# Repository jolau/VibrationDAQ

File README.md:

# VibrationDAQ
Data Acquisition (DAQ) of the [Analog Devices ADcmXL3021](https://www.analog.com/en/products/adcmxl3021.html#product-overview) vibration sensor. The VibrationDAQ was developed as part of an internship at [Wingtra](https://wingtra.com/) by [Jonas Lauener](https://www.jolau.ch/).  

**For any technical questions, please open an issue: https://github.com/jolau/VibrationDAQ/issues/new/choose**

Copyright (c) 2020, Jonas Lauener & Wingtra AG\

## Hardware
- Raspberry Pi 
- [Analog Devices ADcmXL3021](https://www.analog.com/en/products/adcmxl3021.html#product-overview) vibration sensor capabilities
    - [Corrected data sheet](docs/ADcmXL3021_corrected.pdf)
    - Sensor orientation:\
    
    - Mass: 13 g
    - Frequencies up to 110 kHz
    - ±50 g measurement range
    - MFFT mode: Spectral analysis through internal FFT\
    
        - 2048 bins per axis with user configurable bin sizes from 0.42 Hz to 53.7 Hz
        - Windowing options: rectangular, Hanning, flat top
    - MTC mode: Time domain capture\
    
        - 4096 samples per axis
- [Features a status LED](#status-led)

### Pinout Raspberry Pi

|       | pin | pin |       |
|-------|-----|-----|-------|
| RST 1 | 13  |     |       |
| BSY 1 | 15  | 16  | RST 2 |
| 3V3   | 17  | 18  | BSY 2 |
| MOSI  | 19  | 20  | EMPTY |
| MISO  | 21  | 22  | SYNC  |
| SCLK  | 23  | 24  | CE 1  |
| GND   | 25  | 26  | CE 2  |

The vibration sensor only works on the main SPI pins (SPI0) of the Raspberry Pi - the other SPI ports don't support SPI mode 3.

### Custom adapter board
The pins of the ADcmXL3021 vibration sensor can be accessed by using a custom adapter board. The PCB was created by using the software KiCad: [KiCad project files](ADcmXL3021_adapter/ADcmXL3021_adapter.pro)\

## Installation
_In case you want to setup your own VibrationDAQ on a Raspberry Pi:_
1. Install yaml-cpp (as described below)
2. Clone this repo.
3. `cd VibrationDAQ`
4. `mkdir build & cd build`
5. `cmake ..`
6. `sudo make install`

Make sure that you have [enabled SPI](https://www.raspberrypi-spy.co.uk/2014/08/enabling-the-spi-interface-on-the-raspberry-pi/).

You can use it now with `vibration_daq_app [full path to config.yaml]`.

#### Installation of yaml-cpp
1. `wget https://github.com/jbeder/yaml-cpp/archive/yaml-cpp-0.6.3.tar.gz`
2. `tar -xvf yaml-cpp-0.6.3.tar.gz`
3. `cd yaml-cpp-yaml-cpp-0.6.3/`
4. `mkdir build`
5. `cd build`
6. `cmake .. -DYAML_BUILD_SHARED_LIBS=ON`
7. `sudo make install`

### Enable/Disable auto-start
1. Edit config.yaml path in vibration_daq.service file to own needs 
2. `sudo systemctl enable [full path to vibration_daq.service file]`    
    This automatically links the service and enables it. Replace `enable` with `disable` to disable service.

## Dependencies
Many thanks to the authors of the following libraries:
- [yaml-cpp](https://github.com/jbeder/yaml-cpp)
- [loguru](https://github.com/emilk/loguru)
- [c-periphery](https://github.com/vsergeev/c-periphery)
- [date](https://github.com/HowardHinnant/date)

## Usage
### Workflow
1. Connect to the Raspberry Pi and adapt the `~/Documents/config.yaml` to your requirements. Make sure that auto-start is enabled. If it's the first time you use it, test it by running it manually: `vibration_daq_app [full path to config.yaml]`
2. Mount the vibration sensor with the double sided tape [3M™ Adhesive Transfer Tape 950](https://www.digikey.ch/product-detail/en/3m-tc/3-4-5-950/3M9743-ND/2649288). This shouldn't distort the vibration too much.
3. Do your measurement.
4. Download the collected data over SFTP. I recommend to also download the used config file.
6. Open a vibration CSV file in Google Sheets. 
    - For FFT measurement: 
        - Hide the first two data points as these have usually very high magnitude and don't give meaningful information
        - Plot the data using a column chart.  

### Status led
If the status led is enabled in config, it will glow when running:
- Constant glow: data acquisition is running normally
- Blink: measurement completed, saving data to a new csv file

## Config file
Short primer on the syntax of yaml: https://learnxinyminutes.com/docs/yaml/

### Decimation Filter
Setting the right `decimation_factor` is crucial for getting meaningful data. Choose it according to the maximum vibration frequency you're expecting.
Of course, the decimation factor also affects the predefined FIR filters i.e. with a FACTOR_64, the LOW_PASS_10kHz is actually a 156 Hz low pass filter.  
 
| **decimation_factor** | **Effective Sample Rate, fS (SPS)** | **Effective FFT Bin Size, f_MIN (Hz)** | **Effective Maximum FFT Frequency, f_MAX (Hz)** |
|-------------------|---------------------------------|------------------------------------|---------------------------------------------|
| FACTOR_1          | 220000                          | 53.71094                           | 110000                                      |
| FACTOR_2          | 110000                          | 26.85547                           | 55000                                       |
| FACTOR_4          | 55000                           | 13.42773                           | 27500                                       |
| FACTOR_8          | 27500                           | 6.713867                           | 13750                                       |
| FACTOR_16         | 13750                           | 3.356934                           | 6875                                        |
| FACTOR_32         | 6875                            | 1.678467                           | 3437.5                                      |
| FACTOR_64         | 3437.5                          | 0.839233                           | 1718.75                                     |
| FACTOR_128        | 1718.75                         | 0.419617                           | 859.375                                     |

### Spectral average count
The `spectral_avg_count` determines the number of FFT records that the ADcmXL3021 averages when generating the final FFT result. Up to 255 records. Good for getting FFT measurements over longer time periods.

### Calculate measurement duration
#### FFT
4096 samples / (220'000 sample rate / `decimation_factor`) * `spectral_avg_count` = record time [s]

##### Example with FACTOR_64 and 255 spectral averages:
4096 samples / (220000 sample rate / 64) * 255 = 303.84 seconds = 5.06 minutes

#### MTC
4096 samples / (220'000 sample rate / `decimation_factor`) = record time [s]

### Example config with explanation
```yaml
storage_directory: "/home/pi/Documents/"
recordings_count: 2 #number of recurring measurements, infinite if == 0 
external_trigger: false # false: triggering over SPI; 
                        # true: triggering over dedicated pin, useful for triggering multiple sensor at exact same time (connect them to same pin)
external_trigger_pin: 4 # only read if external_trigger == true
status_led: true # enable/disable status led, blinks everytime a vibration file is written
status_led_pin: 21  # only read if status_led == true
sensors:
  - name: sensor1 #will be used for logging and filenames
    busy_pin: 22 #BCM pin number
    reset_pin: 27 #BCM pin number
    spi_path: "/dev/spidev0.0"
    recording_mode: MFFT # MTC and MFFT supported
    MFFT_config: &mfftConfig #only read if recording_mode == MFFT
      decimation_factor: FACTOR_2 #supported: [FACTOR_1 = 0, FACTOR_2 = 1, FACTOR_4 = 2, FACTOR_8 = 3, FACTOR_16 = 4, FACTOR_32 = 5, FACTOR_64 = 6, FACTOR_128 = 7]
      fir_filter: CUSTOM #supported: [NO_FILTER, LOW_PASS_1kHz, LOW_PASS_5kHz, LOW_PASS_10kHz, HIGH_PASS_1kHz, HIGH_PASS_5kHz, HIGH_PASS_10kHz, CUSTOM]
      custom_filter_taps: [6, 21, 53, 107, 193, 316, 480, 686, 930, 1203, 1490, 1774, 2034, 2251, 2407, 2489, 2489, 2407, 2251, 2034, 1774, 1490, 1203, 930, 686, 480, 316, 193, 107, 53, 21, 6]
      spectral_avg_count: 2 # value between 1-255
      window_setting: HANNING #supported: [RECTANGULAR, HANNING, FLAT_TOP]
    MTC_config: #only read if recording_mode == MTC
        decimation_factor: FACTOR_2
        fir_filter: CUSTOM
        custom_filter_taps: [6, 21, 53, 107, 193, 316, 480, 686, 930, 1203, 1490, 1774, 2034, 2251, 2407, 2489, 2489, 2407, 2251, 2034, 1774, 1490, 1203, 930, 686, 480, 316, 193, 107, 53, 21, 6]
  - name: sensor2
    busy_pin: 24
    reset_pin: 23
    spi_path: "/dev/spidev0.1"
    recording_mode: MFFT
    MFFT_config: *mfftConfig #copy config from sensor1 above
```

## Example data
The following data was collected on a self-made vibration bench. The bench consists of an unbalanced mass attached to an electrical motor. 
- [MFFT raw data example](docs/vibration_data_MFFT_2020-06-17T16_08_57.423_sensor1.csv)
    - Plot of MFFT data:\
       
- [MTC raw data example](docs/vibration_data_MTC_2020-06-25T07_34_45.609_sensor1.csv)

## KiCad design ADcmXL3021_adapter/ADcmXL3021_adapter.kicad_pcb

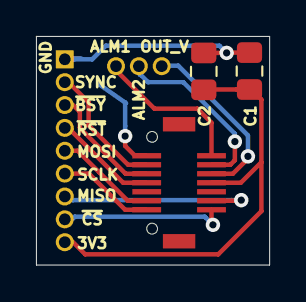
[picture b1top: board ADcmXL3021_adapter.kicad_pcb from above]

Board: 2 copper layers, 13.0 x 12.7 mm, 5 parts (0 on the bottom side), 12 nets.

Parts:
C1: 10UF 25V; C_0805_2012Metric_Pad1.15x1.40mm_HandSolder
C2: 1UF 25V; C_0805_2012Metric_Pad1.15x1.40mm_HandSolder
J1: DF12(3.0)-14DP-0.5V(86); Hirose_DF12(3.0)-14DP-0.5V(86)
J2: Pin Header; PinHeader_1x09_P1.27mm_Vertical
J3: Aux Pin Header; PinHeader_1x03_P1.27mm_Vertical

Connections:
+3V3: C1.1, C2.1, J1.8, J2.9
/ALM1: J1.2, J3.1
/ALM2: J1.4, J3.2
/MISO: J1.12, J2.7
/MOSI: J1.11, J2.5
/OUT_VDDM: J1.6, J3.3
/SCLK: J1.13, J2.6
/SYNC_RTS: J1.3, J2.2
/~BUSY~: J1.5, J2.3
/~CS~: J1.14, J2.8
/~RST~: J1.7, J2.4
GND: C1.2, C2.2, J1.1, J2.1

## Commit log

2020-04-21 moved VibrationDAQ to its own dir
2020-04-21 fixed external triggering & added to config
2020-04-21 config file as app argument
2020-04-21 small fix
2020-04-22 added make install
2020-04-22 better time string
2020-04-27 added install guide
2020-04-27 fix readme
2020-04-27 better logging with multiple sensors
2020-04-27 more compact pin config
2020-04-28 better filenames for multiple sensors
2020-04-30 added cap. for autonull/reset & fft conversion special case handling
2020-04-30 removed old code dump
2020-05-04 comments
2020-05-05 switched to utc time for filenames
2020-05-05 pwm led
    not stable
2020-05-05 status led simple & added to config
2020-05-05 consistency renaming
2020-05-06 fixed hardcoded led pin
2020-05-15 add service file
2020-05-15 added autostart to readme
2020-05-15 updated config descirption in README
2020-05-20 initial version of temp_daq
2020-06-03 improve docs
2020-06-03 added blinking
2020-06-18 cleanup & docs
2020-06-19 clean up
2020-06-23 improved docs
2020-06-24 added pinout
2020-06-26 added logging of trigger mode
2020-06-26 better gitignore
2020-06-29 added image
2020-07-02 more highres image
2020-07-02 added adapter board to git
2020-07-02 improved naming and added more comments
2020-07-16 added licences and info for public
2020-07-16 improved readme
2020-07-20 removed deployment
2022-08-28 Update README.md
    added clarificatation to usage

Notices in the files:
README.md:
License: MPL 2.0
